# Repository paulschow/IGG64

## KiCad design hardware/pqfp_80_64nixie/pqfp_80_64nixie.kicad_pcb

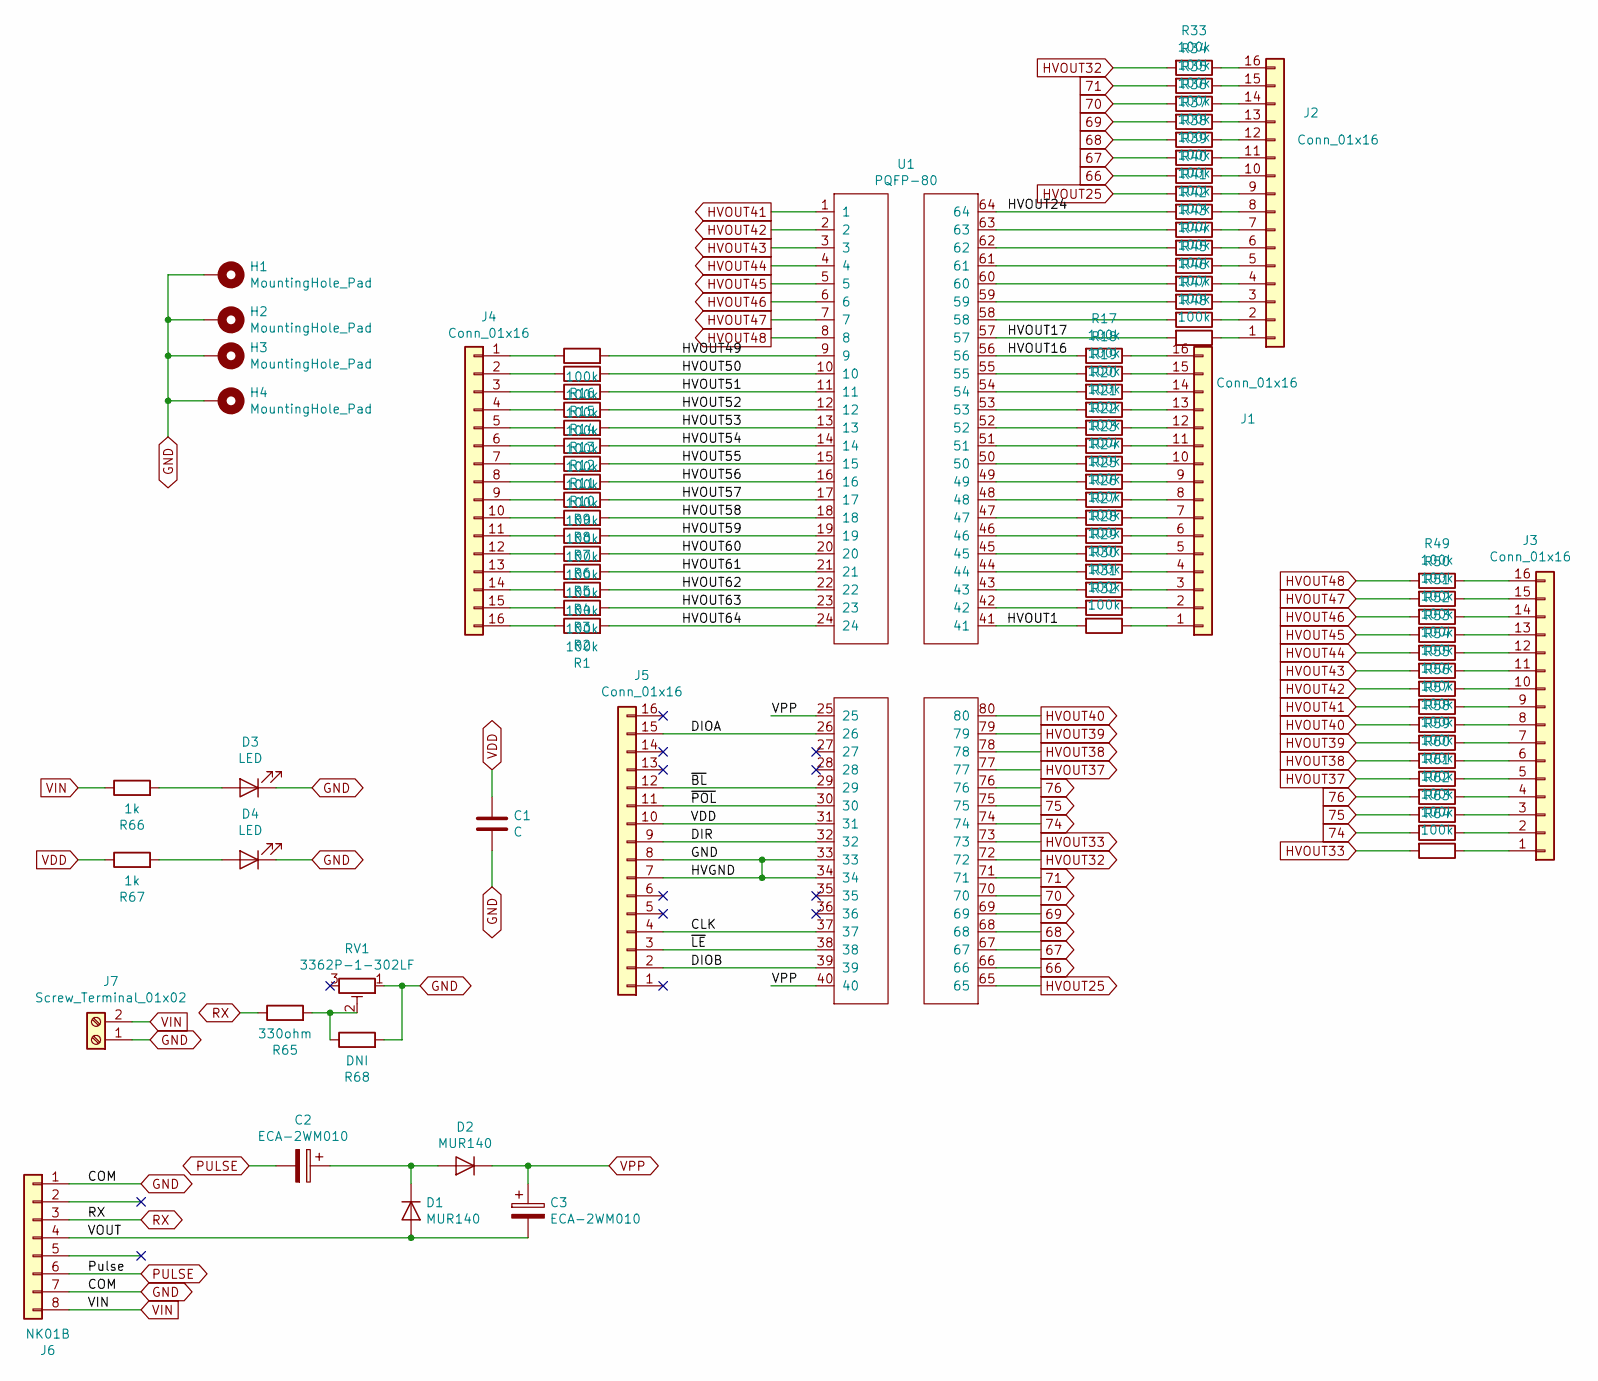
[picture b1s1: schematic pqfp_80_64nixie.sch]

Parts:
C1: C; C_1206_3216Metric_Pad1.42x1.75mm_HandSolder
C2, C3: ECA-2WM010; CP_Radial_D8.0mm_P3.50mm
D1, D2: MUR140; D_DO-41_SOD81_P10.16mm_Horizontal
D3, D4: LED; LED_D10.0mm
H1, H2, H3, H4: MountingHole_Pad; MountingHole_3.2mm_M3_ISO14580_Pad
J1, J2, J3, J4, J5: Conn_01x16; PinSocket_2x08_P2.54mm_Vertical_SMD
J6: NK01B; PinSocket_1x08_P2.54mm_Vertical
J7: Screw_Terminal_01x02; TerminalBlock_bornier-2_P5.08mm
R1, R2, R3, R4, R5, R6, R7, R8, R9, R10, R11, R12, R13, R14, R15, R16, R17, R18, R19, R20, R21, R22, R23, R24, R25, R26, R27, R28, R29, R30, R31, R32, R33, R34, R35, R36, R37, R38, R39, R40, R41, R42, R43, R44, R45, R46, R47, R48, R49, R50, R51, R52, R53, R54, R55, R56, R57, R58, R59, R60, R61, R62, R63, R64: 100k; R_1206_3216Metric
R65: 330ohm; R_Axial_DIN0207_L6.3mm_D2.5mm_P10.16mm_Horizontal
R66, R67: 1k; R_Axial_DIN0207_L6.3mm_D2.5mm_P10.16mm_Horizontal
R68: DNI; R_Axial_DIN0207_L6.3mm_D2.5mm_P10.16mm_Horizontal
RV1: 3362P-1-302LF; Potentiometer_Bourns_3386P_Vertical
U1: PQFP-80; PQFP-80_14x20mm_P0.8mm

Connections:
66: R39.2, U1.66
67: R38.2, U1.67
68: R37.2, U1.68
69: R36.2, U1.69
70: R35.2, U1.70
71: R34.2, U1.71
74: R63.2, U1.74
75: R62.2, U1.75
76: R61.2, U1.76
/CLK: J5.4, U1.37
/DIOA: J5.15, U1.26
/DIOB: J5.2, U1.39
/DIR: J5.9, U1.32
/HVOUT1: R32.2, U1.41
/HVOUT16: R17.2, U1.56
/HVOUT17: R48.2, U1.57
/HVOUT24: R41.2, U1.64
/HVOUT49: R16.2, U1.9
/HVOUT50: R15.2, U1.10
/HVOUT51: R14.2, U1.11
/HVOUT52: R13.2, U1.12
/HVOUT53: R12.2, U1.13
/HVOUT54: R11.2, U1.14
/HVOUT55: R10.2, U1.15
/HVOUT56: R9.2, U1.16
/HVOUT57: R8.2, U1.17
/HVOUT58: R7.2, U1.18
/HVOUT59: R6.2, U1.19
/HVOUT60: R5.2, U1.20
/HVOUT61: R4.2, U1.21
/HVOUT62: R3.2, U1.22
/HVOUT63: R2.2, U1.23
/HVOUT64: R1.2, U1.24
/VOUT: C3.2, D1.2 (A), J6.4
/~BL: J5.12, U1.29
/~LE: J5.3, U1.38
/~POL: J5.11, U1.30
GND: C1.2, D3.1 (K), D4.1 (K), H1.1, H2.1, H3.1, H4.1, J5.7, J5.8, J6.1, J6.7, J7.1, R68.2, RV1.1, U1.33, U1.34
HVOUT25: R40.2, U1.65
HVOUT32: R33.2, U1.72
HVOUT33: R64.2, U1.73
HVOUT37: R60.2, U1.77
HVOUT38: R59.2, U1.78
HVOUT39: R58.2, U1.79
HVOUT40: R57.2, U1.80
HVOUT41: R56.2, U1.1
HVOUT42: R55.2, U1.2
HVOUT43: R54.2, U1.3
HVOUT44: R53.2, U1.4
HVOUT45: R52.2, U1.5
HVOUT46: R51.2, U1.6
HVOUT47: R50.2, U1.7
HVOUT48: R49.2, U1.8
unnamed: C2.1, D1.1 (K), D2.2 (A)
unnamed: D3.2 (A), R66.2
unnamed: D4.2 (A), R67.2
unnamed: J1.1, R32.1
unnamed: J1.2, R31.1
unnamed: J1.3, R30.1
unnamed: J1.4, R29.1
unnamed: J1.5, R28.1
unnamed: J1.6, R27.1
unnamed: J1.7, R26.1
unnamed: J1.8, R25.1
unnamed: J1.9, R24.1
unnamed: J1.10, R23.1
unnamed: J1.11, R22.1
unnamed: J1.12, R21.1
unnamed: J1.13, R20.1
unnamed: J1.14, R19.1
unnamed: J1.15, R18.1
unnamed: J1.16, R17.1
unnamed: J2.1, R48.1
unnamed: J2.2, R47.1
unnamed: J2.3, R46.1
unnamed: J2.4, R45.1
unnamed: J2.5, R44.1
unnamed: J2.6, R43.1
unnamed: J2.7, R42.1
unnamed: J2.8, R41.1
unnamed: J2.9, R40.1
unnamed: J2.10, R39.1
unnamed: J2.11, R38.1
unnamed: J2.12, R37.1
unnamed: J2.13, R36.1
unnamed: J2.14, R35.1
unnamed: J2.15, R34.1
unnamed: J2.16, R33.1
unnamed: J3.1, R64.1
unnamed: J3.2, R63.1
unnamed: J3.3, R62.1
unnamed: J3.4, R61.1
unnamed: J3.5, R60.1
unnamed: J3.6, R59.1
unnamed: J3.7, R58.1
unnamed: J3.8, R57.1
unnamed: J3.9, R56.1
unnamed: J3.10, R55.1
unnamed: J3.11, R54.1
unnamed: J3.12, R53.1
unnamed: J3.13, R52.1
unnamed: J3.14, R51.1
unnamed: J3.15, R50.1
unnamed: J3.16, R49.1
unnamed: J4.1, R16.1
unnamed: J4.2, R15.1
unnamed: J4.3, R14.1
unnamed: J4.4, R13.1
unnamed: J4.5, R12.1
unnamed: J4.6, R11.1
unnamed: J4.7, R10.1
unnamed: J4.8, R9.1
unnamed: J4.9, R8.1
unnamed: J4.10, R7.1
unnamed: J4.11, R6.1
unnamed: J4.12, R5.1
unnamed: J4.13, R4.1
unnamed: J4.14, R3.1
unnamed: J4.15, R2.1
unnamed: J4.16, R1.1
unnamed: R18.2, U1.55
unnamed: R19.2, U1.54
unnamed: R20.2, U1.53
unnamed: R21.2, U1.52
unnamed: R22.2, U1.51
unnamed: R23.2, U1.50
unnamed: R24.2, U1.49
unnamed: R25.2, U1.48
unnamed: R26.2, U1.47
unnamed: R27.2, U1.46
unnamed: R28.2, U1.45
unnamed: R29.2, U1.44
unnamed: R30.2, U1.43
unnamed: R31.2, U1.42
unnamed: R42.2, U1.63
unnamed: R43.2, U1.62
unnamed: R44.2, U1.61
unnamed: R45.2, U1.60
unnamed: R46.2, U1.59
unnamed: R47.2, U1.58
unnamed: R65.2, R68.1, RV1.2
PULSE: C2.2, J6.6
RX: J6.3, R65.1
VDD: C1.1, J5.10, R67.1, U1.31
VIN: J6.8, J7.2, R66.1
VPP: C3.1, D2.1 (K), U1.25, U1.40

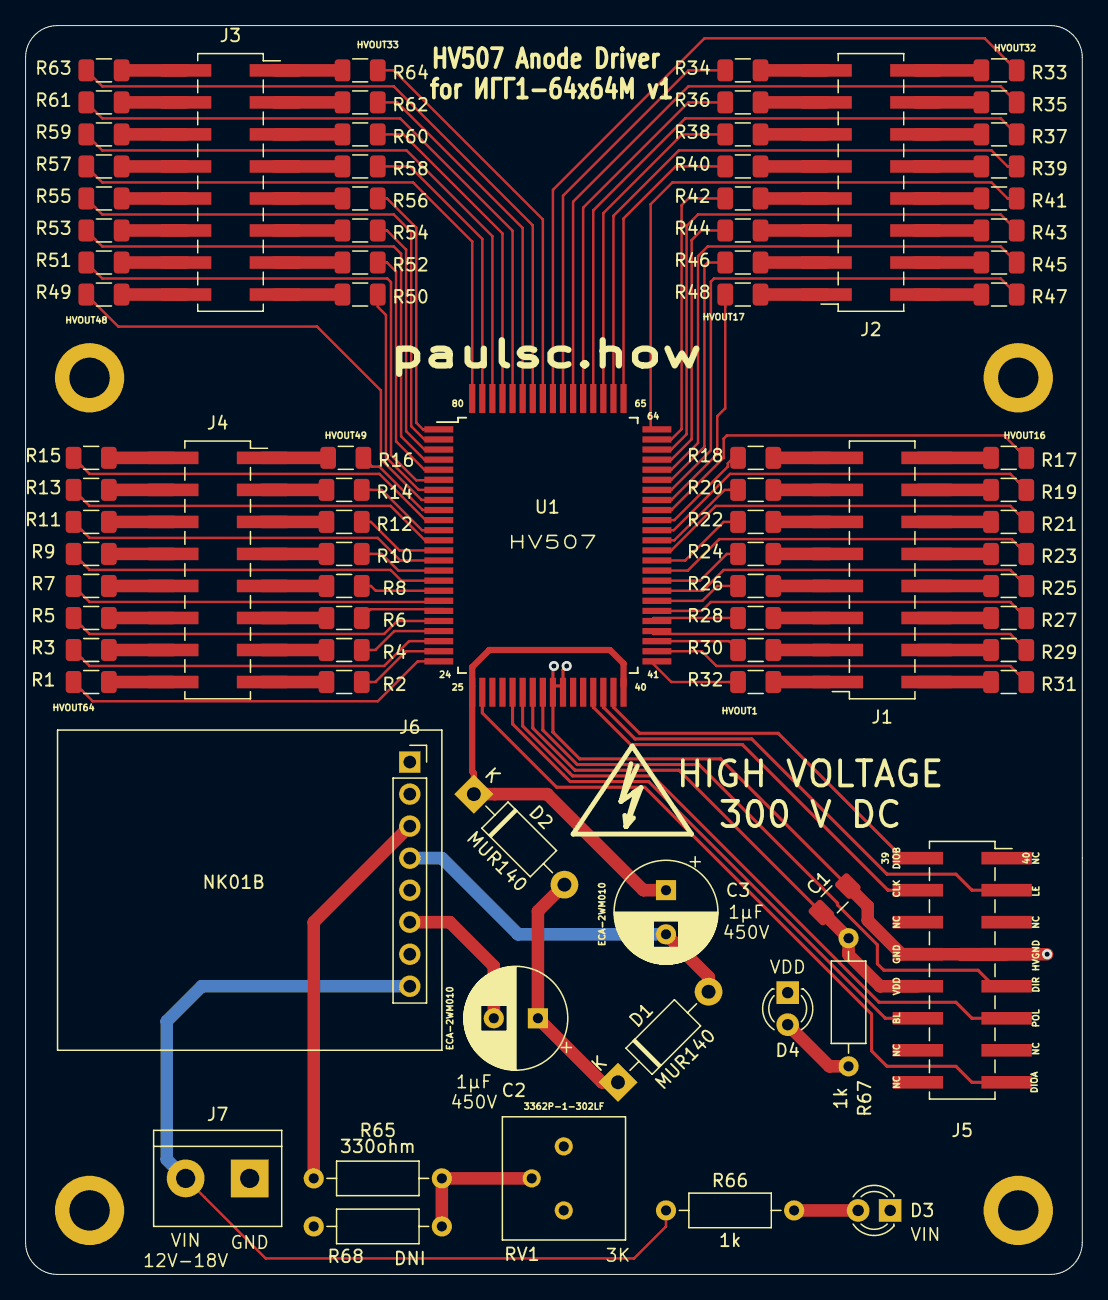
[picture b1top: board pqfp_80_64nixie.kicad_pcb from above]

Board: 2 copper layers, 83.8 x 99.1 mm, 88 parts (0 on the bottom side), 146 nets.

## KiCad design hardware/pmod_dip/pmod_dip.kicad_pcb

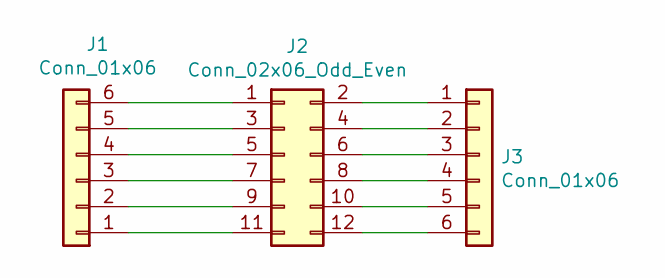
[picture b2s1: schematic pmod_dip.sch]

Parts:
J1, J3: Conn_01x06; PinHeader_1x06_P2.54mm_Vertical
J2: Conn_02x06_Odd_Even; PinHeader_2x06_P2.54mm_Vertical

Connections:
unnamed: J1.1, J2.11
unnamed: J1.2, J2.9
unnamed: J1.3, J2.7
unnamed: J1.4, J2.5
unnamed: J1.5, J2.3
unnamed: J1.6, J2.1
unnamed: J2.2, J3.1
unnamed: J2.4, J3.2
unnamed: J2.6, J3.3
unnamed: J2.8, J3.4
unnamed: J2.10, J3.5
unnamed: J2.12, J3.6

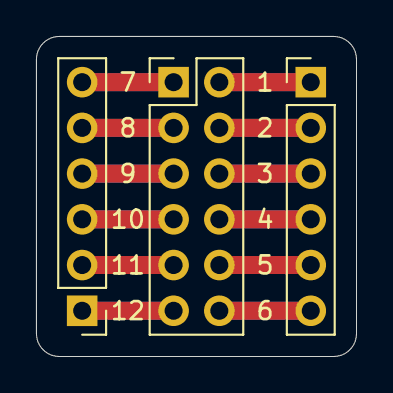
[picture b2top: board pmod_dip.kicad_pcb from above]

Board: 2 copper layers, 17.8 x 17.8 mm, 3 parts (0 on the bottom side), 12 nets.

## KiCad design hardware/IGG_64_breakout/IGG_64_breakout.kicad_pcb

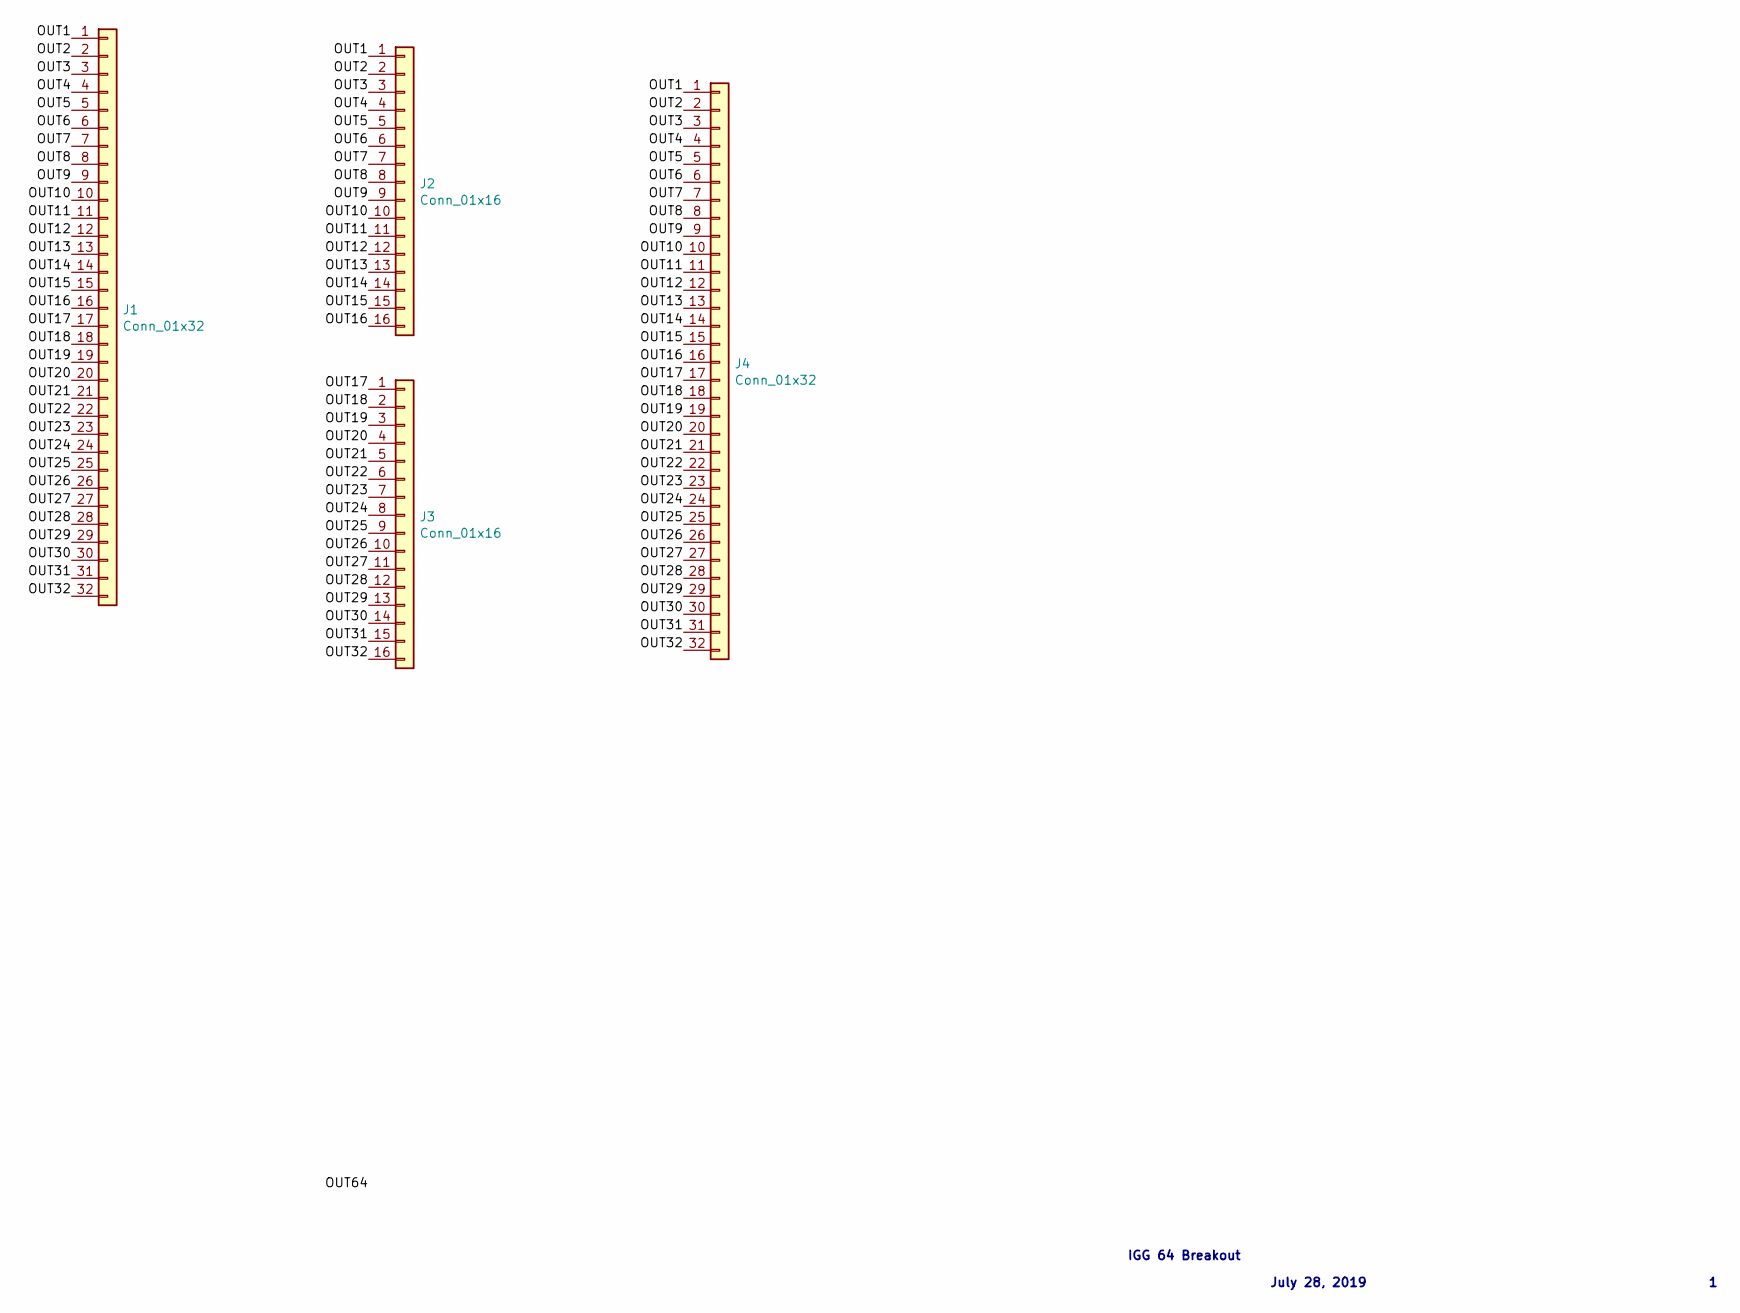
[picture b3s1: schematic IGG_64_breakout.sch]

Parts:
J1: Conn_01x32; igg64_cast_32
J2, J3: Conn_01x16; Shrouded_PinHeader_2x08_P2.54mm_Vertical_SMD
J4: Conn_01x32; PinSocket_1x32_P2.54mm_Vertical

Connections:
/OUT1: J1.1, J2.1, J4.1
/OUT2: J1.2, J2.2, J4.2
/OUT3: J1.3, J2.3, J4.3
/OUT4: J1.4, J2.4, J4.4
/OUT5: J1.5, J2.5, J4.5
/OUT6: J1.6, J2.6, J4.6
/OUT7: J1.7, J2.7, J4.7
/OUT8: J1.8, J2.8, J4.8
/OUT9: J1.9, J2.9, J4.9
/OUT10: J1.10, J2.10, J4.10
/OUT11: J1.11, J2.11, J4.11
/OUT12: J1.12, J2.12, J4.12
/OUT13: J1.13, J2.13, J4.13
/OUT14: J1.14, J2.14, J4.14
/OUT15: J1.15, J2.15, J4.15
/OUT16: J1.16, J2.16, J4.16
/OUT17: J1.17, J3.1, J4.17
/OUT18: J1.18, J3.2, J4.18
/OUT19: J1.19, J3.3, J4.19
/OUT20: J1.20, J3.4, J4.20
/OUT21: J1.21, J3.5, J4.21
/OUT22: J1.22, J3.6, J4.22
/OUT23: J1.23, J3.7, J4.23
/OUT24: J1.24, J3.8, J4.24
/OUT25: J1.25, J3.9, J4.25
/OUT26: J1.26, J3.10, J4.26
/OUT27: J1.27, J3.11, J4.27
/OUT28: J1.28, J3.12, J4.28
/OUT29: J1.29, J3.13, J4.29
/OUT30: J1.30, J3.14, J4.30
/OUT31: J1.31, J3.15, J4.31
/OUT32: J1.32, J3.16, J4.32

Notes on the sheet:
IGG 64 Breakout
July 28, 2019

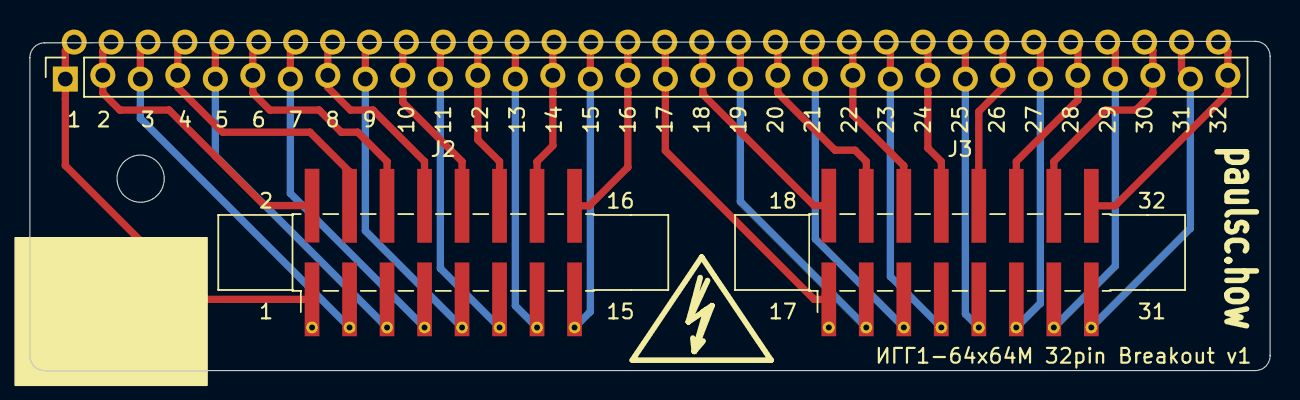
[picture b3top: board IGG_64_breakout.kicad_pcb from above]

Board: 2 copper layers, 84.0 x 22.3 mm, 4 parts (0 on the bottom side), 32 nets.

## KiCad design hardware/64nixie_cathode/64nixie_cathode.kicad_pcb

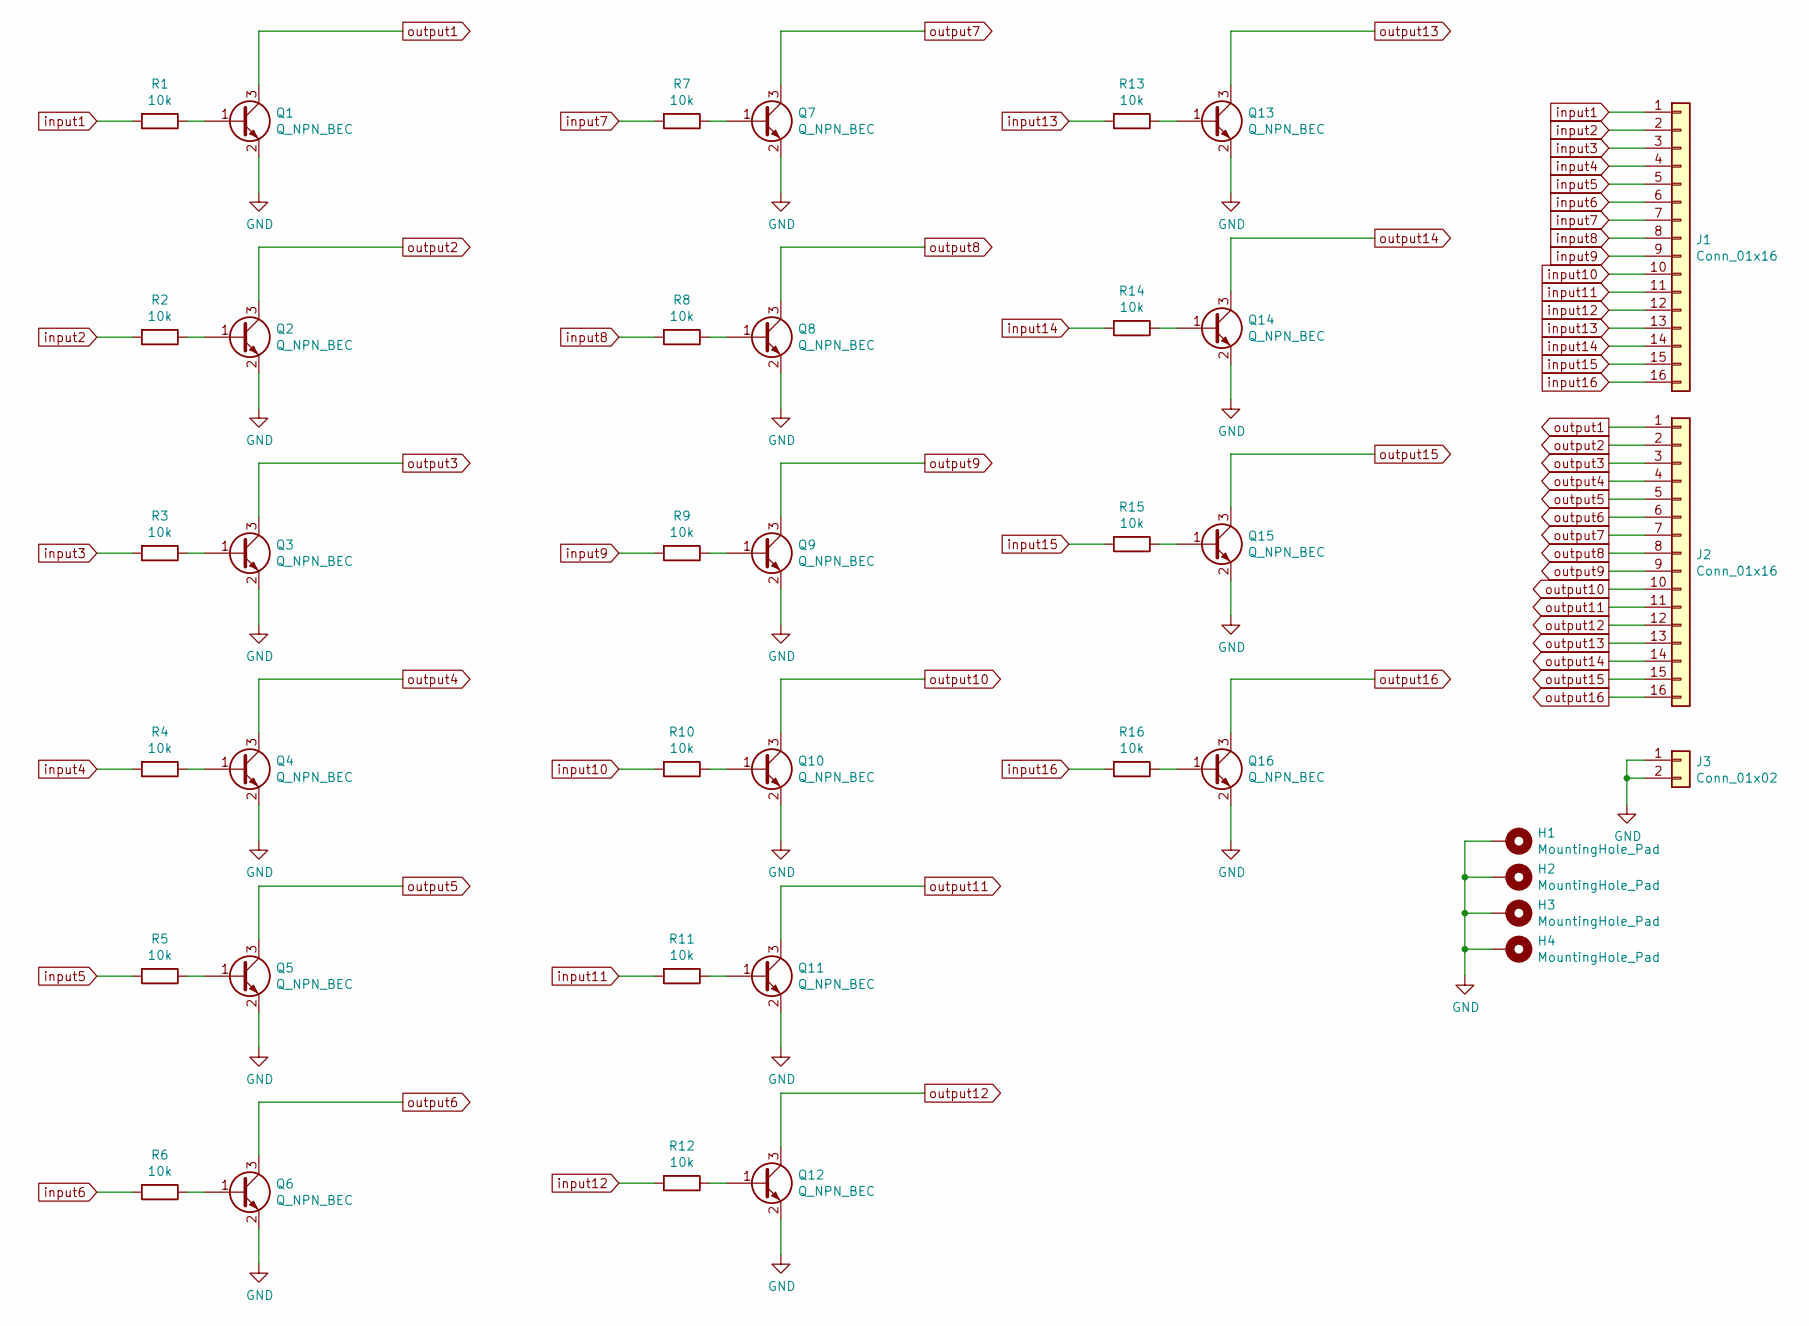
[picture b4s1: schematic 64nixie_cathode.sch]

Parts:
H1, H2, H3, H4: MountingHole_Pad; MountingHole_3.2mm_M3_ISO14580_Pad
J1, J2: Conn_01x16; PinSocket_2x08_P2.54mm_Vertical_SMD
J3: Conn_01x02; PinSocket_1x02_P2.54mm_Vertical
Q1, Q2, Q3, Q4, Q5, Q6, Q7, Q8, Q9, Q10, Q11, Q12, Q13, Q14, Q15, Q16: Q_NPN_BEC; SOT-23
R1, R2, R3, R4, R5, R6, R7, R8, R9, R10, R11, R12, R13, R14, R15, R16: 10k; R_1206_3216Metric

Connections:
GND: H1.1, H2.1, H3.1, H4.1, J3.1, J3.2, Q1.2 (E), Q2.2 (E), Q3.2 (E), Q4.2 (E), Q5.2 (E), Q6.2 (E), Q7.2 (E), Q8.2 (E), Q9.2 (E), Q10.2 (E), Q11.2 (E), Q12.2 (E), Q13.2 (E), Q14.2 (E), Q15.2 (E), Q16.2 (E)
unnamed: Q1.1 (B), R1.1
unnamed: Q2.1 (B), R2.1
unnamed: Q3.1 (B), R3.1
unnamed: Q4.1 (B), R4.1
unnamed: Q5.1 (B), R5.1
unnamed: Q6.1 (B), R6.1
unnamed: Q7.1 (B), R7.1
unnamed: Q8.1 (B), R8.1
unnamed: Q9.1 (B), R9.1
unnamed: Q10.1 (B), R10.1
unnamed: Q11.1 (B), R11.1
unnamed: Q12.1 (B), R12.1
unnamed: Q13.1 (B), R13.1
unnamed: Q14.1 (B), R14.1
unnamed: Q15.1 (B), R15.1
unnamed: Q16.1 (B), R16.1
input1: J1.1, R1.2
input2: J1.2, R2.2
input3: J1.3, R3.2
input4: J1.4, R4.2
input5: J1.5, R5.2
input6: J1.6, R6.2
input7: J1.7, R7.2
input8: J1.8, R8.2
input9: J1.9, R9.2
input10: J1.10, R10.2
input11: J1.11, R11.2
input12: J1.12, R12.2
input13: J1.13, R13.2
input14: J1.14, R14.2
input15: J1.15, R15.2
input16: J1.16, R16.2
output1: J2.1, Q1.3 (C)
output2: J2.2, Q2.3 (C)
output3: J2.3, Q3.3 (C)
output4: J2.4, Q4.3 (C)
output5: J2.5, Q5.3 (C)
output6: J2.6, Q6.3 (C)
output7: J2.7, Q7.3 (C)
output8: J2.8, Q8.3 (C)
output9: J2.9, Q9.3 (C)
output10: J2.10, Q10.3 (C)
output11: J2.11, Q11.3 (C)
output12: J2.12, Q12.3 (C)
output13: J2.13, Q13.3 (C)
output14: J2.14, Q14.3 (C)
output15: J2.15, Q15.3 (C)
output16: J2.16, Q16.3 (C)

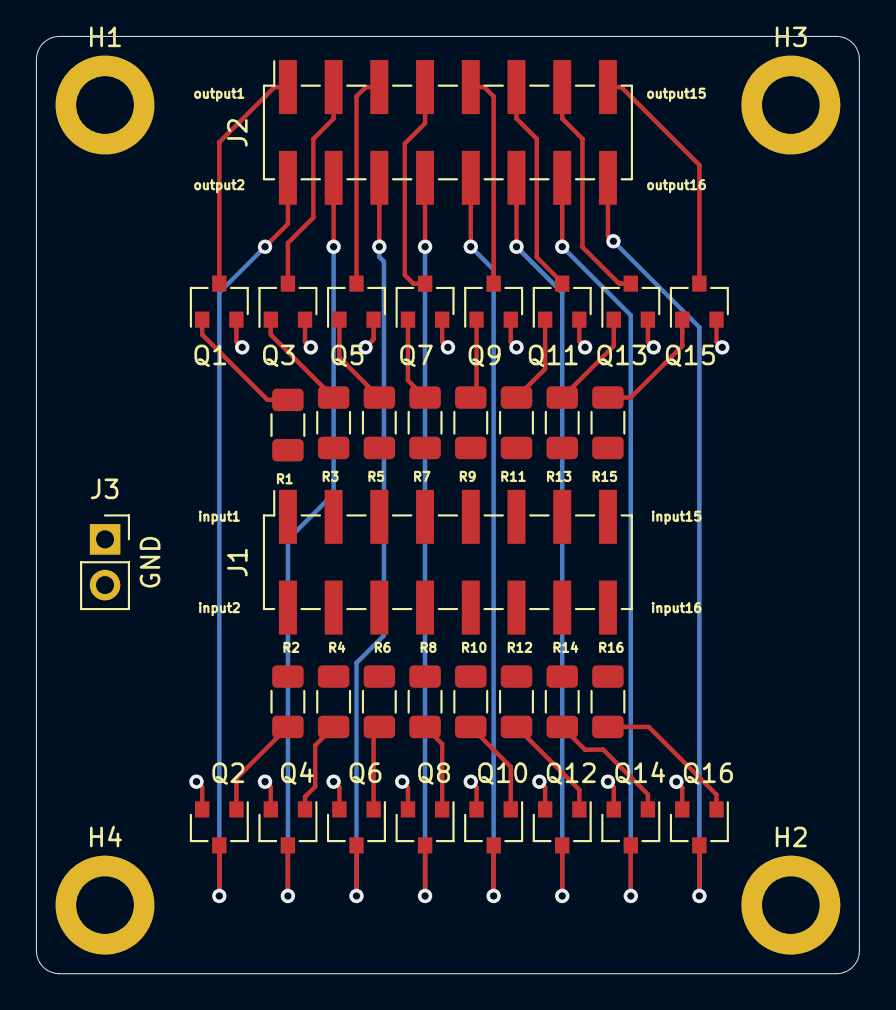
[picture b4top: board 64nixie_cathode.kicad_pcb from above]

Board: 2 copper layers, 45.7 x 52.1 mm, 39 parts (0 on the bottom side), 49 nets.

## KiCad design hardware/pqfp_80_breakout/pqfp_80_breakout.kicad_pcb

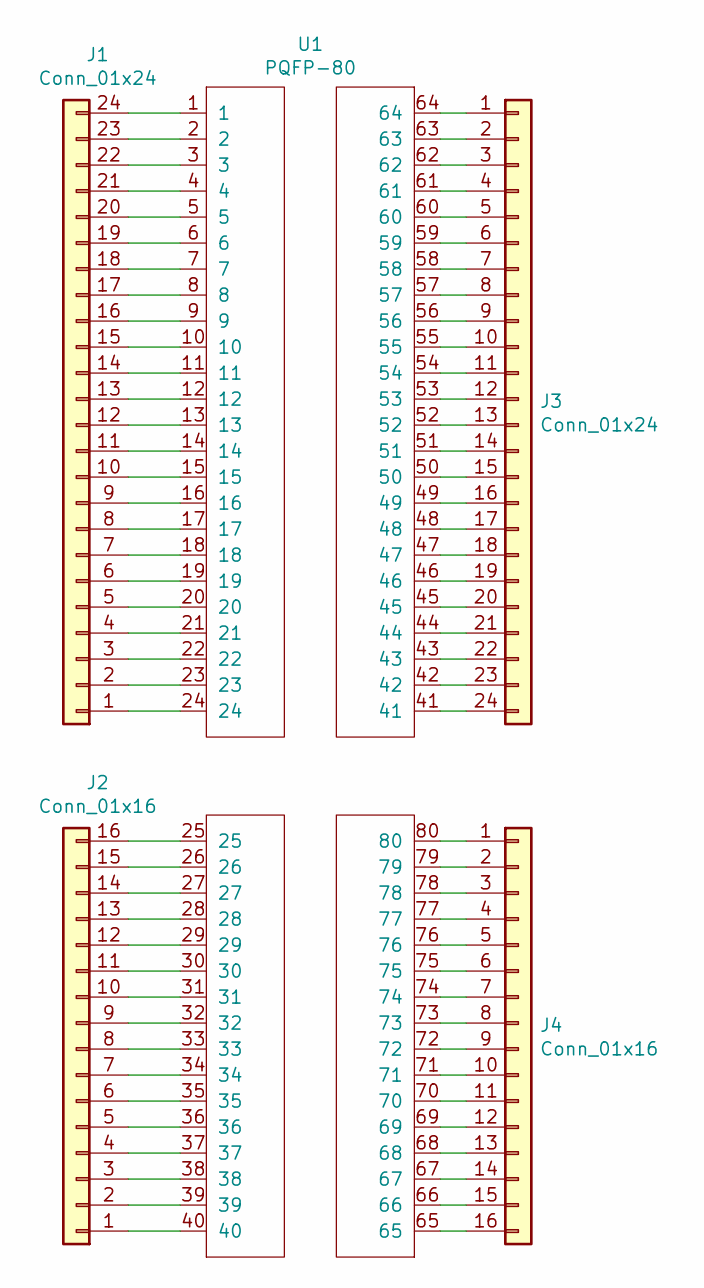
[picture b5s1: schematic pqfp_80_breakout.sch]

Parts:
J1, J3: Conn_01x24; PinHeader_2x12_P2.54mm_Vertical
J2, J4: Conn_01x16; PinHeader_2x08_P2.54mm_Vertical
U1: PQFP-80; PQFP-80_14x20mm_P0.8mm

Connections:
unnamed: J1.1, U1.24
unnamed: J1.2, U1.23
unnamed: J1.3, U1.22
unnamed: J1.4, U1.21
unnamed: J1.5, U1.20
unnamed: J1.6, U1.19
unnamed: J1.7, U1.18
unnamed: J1.8, U1.17
unnamed: J1.9, U1.16
unnamed: J1.10, U1.15
unnamed: J1.11, U1.14
unnamed: J1.12, U1.13
unnamed: J1.13, U1.12
unnamed: J1.14, U1.11
unnamed: J1.15, U1.10
unnamed: J1.16, U1.9
unnamed: J1.17, U1.8
unnamed: J1.18, U1.7
unnamed: J1.19, U1.6
unnamed: J1.20, U1.5
unnamed: J1.21, U1.4
unnamed: J1.22, U1.3
unnamed: J1.23, U1.2
unnamed: J1.24, U1.1
unnamed: J2.1, U1.40
unnamed: J2.2, U1.39
unnamed: J2.3, U1.38
unnamed: J2.4, U1.37
unnamed: J2.5, U1.36
unnamed: J2.6, U1.35
unnamed: J2.7, U1.34
unnamed: J2.8, U1.33
unnamed: J2.9, U1.32
unnamed: J2.10, U1.31
unnamed: J2.11, U1.30
unnamed: J2.12, U1.29
unnamed: J2.13, U1.28
unnamed: J2.14, U1.27
unnamed: J2.15, U1.26
unnamed: J2.16, U1.25
unnamed: J3.1, U1.64
unnamed: J3.2, U1.63
unnamed: J3.3, U1.62
unnamed: J3.4, U1.61
unnamed: J3.5, U1.60
unnamed: J3.6, U1.59
unnamed: J3.7, U1.58
unnamed: J3.8, U1.57
unnamed: J3.9, U1.56
unnamed: J3.10, U1.55
unnamed: J3.11, U1.54
unnamed: J3.12, U1.53
unnamed: J3.13, U1.52
unnamed: J3.14, U1.51
unnamed: J3.15, U1.50
unnamed: J3.16, U1.49
unnamed: J3.17, U1.48
unnamed: J3.18, U1.47
unnamed: J3.19, U1.46
unnamed: J3.20, U1.45
unnamed: J3.21, U1.44
unnamed: J3.22, U1.43
unnamed: J3.23, U1.42
unnamed: J3.24, U1.41
unnamed: J4.1, U1.80
unnamed: J4.2, U1.79
unnamed: J4.3, U1.78
unnamed: J4.4, U1.77
unnamed: J4.5, U1.76
unnamed: J4.6, U1.75
unnamed: J4.7, U1.74
unnamed: J4.8, U1.73
unnamed: J4.9, U1.72
unnamed: J4.10, U1.71
unnamed: J4.11, U1.70
unnamed: J4.12, U1.69
unnamed: J4.13, U1.68
unnamed: J4.14, U1.67
unnamed: J4.15, U1.66
unnamed: J4.16, U1.65

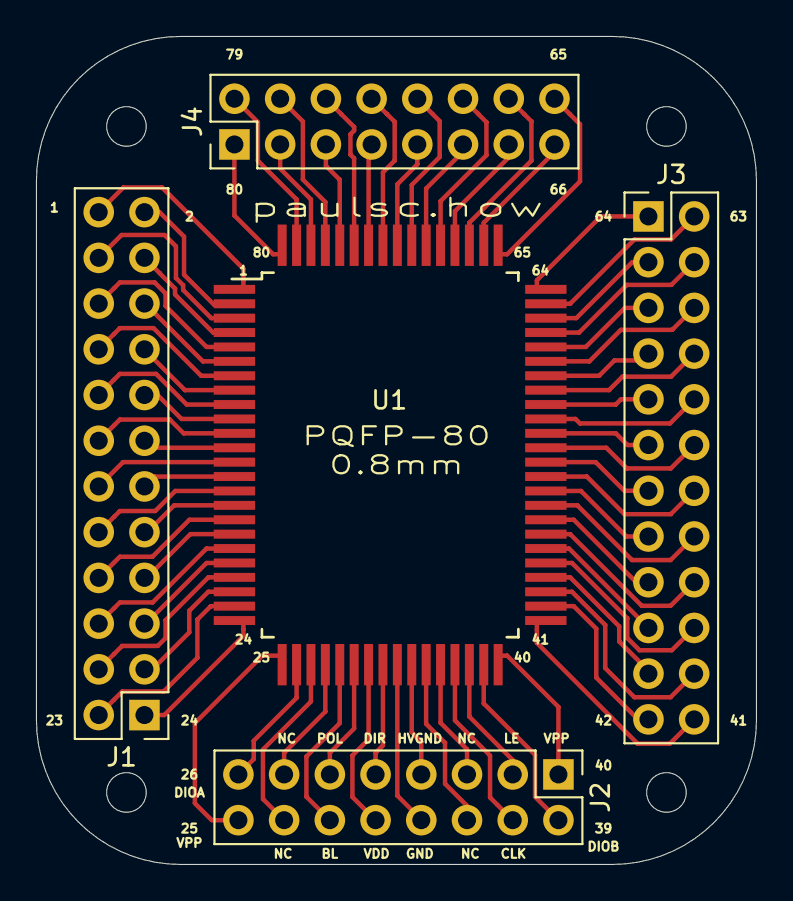
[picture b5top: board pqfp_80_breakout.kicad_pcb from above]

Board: 2 copper layers, 40.0 x 46.0 mm, 5 parts (0 on the bottom side), 80 nets.

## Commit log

2020-02-24 Fixing NK01B pinout
2020-02-24 New header footprint
